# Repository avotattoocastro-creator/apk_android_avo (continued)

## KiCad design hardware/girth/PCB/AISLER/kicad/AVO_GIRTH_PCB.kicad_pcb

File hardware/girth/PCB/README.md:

# AVO GIRTH · placa de la cincha · REV B (ESP32-C3)

Placa propia para la cápsula de la cincha (REV 5.8.1), montada por JLCPCB: **una sola PCB de 4 capas** del tamaño de la
bandeja, con **conector para la batería** (JST SH 1,0) y **pads para soldar la bobina Qi** y el reed.

**Por qué REV B:** JLCPCB no tiene el ESP32-C6-MINI-1U-N4 de la REV A (0 uds. el 2026-10-29). La REV B usa el
**ESP32-C3-MINI-1U-N4** (C2911374, 1191 uds.), cambia el BNO085 (19,50 US$, 80 uds.) por **LSM6DS3TR-C + MMC5983MA**
y el relé biestable por un **enclavamiento con MOSFET**: mismas funciones, ~50 % menos de coste por placa
(`out_stock/COSTE.md`). La REV A queda congelada en `../PCB_REV_A_C6`.

**Estado:** diseño generado y comprobado en CI con KiCad 9 (`out/`). **NO VERIFICADO** en hardware: no se ha
fabricado ni medido ninguna placa.

## Qué lleva
| Bloque | Pieza | Notas |
|---|---|---|
| MCU | ESP32-C3-MINI-1U-N4 (U4) | antena externa por el conector de 3.ª generación del módulo (**W.FL / MHF III**, no U.FL). Alternativa: -H4 (C3013922, 105 °C, misma memoria) |
| IMU | LSM6DS3TR-C (U5) + MMC5983MA (U7) por **I²C** | 9 ejes brutos como pide el protocolo de la cincha; la huella de U5 admite el LSM6DSV16X |
| Qi | BQ51013B (U1), salida 5 V | bobina Ø25 a los pads L1/L2; condensadores de resonancia **a ajustar** (`DOCS/AJUSTE_QI.md`) |
| Carga | BQ24072 (U2) con camino de potencia | 270 mA de carga (0,54 C), entrada limitada a 462 mA (< 494 mA del Qi), NTC en placa (RT2) |
| USB-C | J1 + ESD (U6) | programación y consola; entra en el BQ51013B por AD/AD-EN (Q1/Q2) y **también carga** |
| 3,3 V | RT9080-33 (U3) | 600 mA, 2 µA de consumo propio |
| Batería | J2 JST SH 1,0 (pin 1 = +) | el cable pasa por la ranura fresada junto al borde −X |
| Reed | pads SW1/SW2 (SW2 al + de la batería) | enciende por flanco y se lee en GPIO1 (Q16) |
| **Corte de batería** | **Q10 (PMOS) + Q11 (NMOS) + D10–D13 (BAV70)** | **≤ 2 µA apagada** fuera del soporte (máx. de hoja a 25 °C; ≈ 7–8 µA dentro); ver abajo |

## Corte de batería (enclavamiento con MOSFET)
- **Se enciende solo**, sin firmware: al **cerrarse** el reed (C40 da un impulso de ≈ 2,5 s, con la corriente por el
  reed limitada a 19 mA y rearmado en ~2–3 s tras abrirse) o con 5 V de la base Qi o del USB (D10, mientras estén).
- **El firmware lo mantiene** con PWR_HOLD (GPIO5) = 1, que pone lo primero al arrancar. Si el ESP32 se reinicia, C41
  sostiene el corte ~1,2 s.
- **Se apaga desde el ESP32**: PWR_HOLD = 0 → el corte se abre en ~2,7 s. Funciona también con el reed cerrado (el reed
  actúa por flanco), así que el **apagado remoto** sigue siendo posible en el soporte.
- **Nunca queda bloqueado al cargar**: con 5 V presentes el corte está cerrado pase lo que pase en el firmware.
- **Batería agotada**: con la base puesta, el diodo interno de Q10 deja precargar la celda y luego Q10 conduce.
- Cálculos en `DOCS/ANALISIS_ELECTRICO.md` §3 (red del reed revisada tras una revisión independiente). Respecto al relé de la REV A: no necesita rebaje en la tapa ni
  condensadores de 220 µF, no tiene polaridad que adivinar (R40/R41 desaparecen) y no lleva imán junto a la IMU.

## Pines del ESP32-C3 (firmware V0.3.0: `firmware/girth/V0_3_0_C3`)
| GPIO | Función | Nota |
|---|---|---|
| 0 | IMU_INT (INT1 del LSM6) | despierta |
| 1 | REED (LOW = cápsula en el soporte) | despierta |
| 2 | I²C SCL | strapping: 1 al arrancar gracias al pull-up de 4,7 k |
| 3 | BAT_ADC (ADC1_CH3) | divisor 1 MΩ / 1 MΩ → V_bat / 2 |
| 4 | CHG_PG (LOW = hay 5 V) | despierta |
| 5 | PWR_HOLD | 1 = mantener la alimentación |
| 6 | I²C SDA | |
| 7 | CHG_STAT (LOW = cargando) | |
| 8 | LED rojo (activo bajo) | strapping: 1 al arrancar |
| 9 | BOOT (pad TP2) | strapping; 5 s pulsado = olvidar la espalda |
| 10 | QI_CHG (LOW = el Qi entrega potencia) | |
| 18 / 19 | USB D− / D+ | USB-Serial-JTAG |
| 20 / 21 | RXD0 / TXD0 (pads TP5 / TP4) | UART0 de la ROM: registro y recuperación |

**Reglas para el firmware:** PWR_HOLD = 1 lo primero; fuera del soporte 3 s sin carga → apagar; batería < 3,30 V →
apagar; en la base Qi fuera del soporte → sueño profundo. Detalle en `firmware/girth/V0_3_0_C3/DIFERENCIAS_C6_C3.md`.

## Programación y recuperación
Por el USB-C interno (USB-Serial-JTAG) con esptool o Arduino: `AVO_GIRTH_V0_3_0_C3_COMPLETO.bin` en 0x0. Si el
firmware no arranca: mantener BOOT (TP2) a masa al encender para entrar en modo descarga, o usar el UART0 (TP4/TP5).
**AVO Update todavía solo instala en el ESP32-C6**: hay que adaptarlo (id de chip 5 y vigilantes del C3) antes de
usarlo con esta placa.

## Consumo estimado
- **Apagada** (fuera del soporte): ≤ 2 µA (fugas de Q10 y de Q11 por R40, máx. de hoja a 25 °C; más con calor) + autodescarga de la celda. **Dentro del soporte** (reed
  cerrado): ≈ 7–8 µA por R45 y R49/R50 (simulado en la auditoría REV B, `AUDITORIA_REV_B/spice`).
- **Funcionando**: *corregido en la auditoría REV B* — con el firmware V0.3.0 (radio sin ahorro, `WIFI_PS_NONE`)
  ≈ 94 mA → **≈ 5 h** con 500 mAh (4 h con la celda envejecida); con ahorro de radio ≈ 45 mA → ≈ 10 h. Cálculo en
  `AUDITORIA_REV_B/autonomia/` (sin medir). La cifra anterior (25–45 mA, 11–20 h) no contaba el receptor encendido.
- **En la base Qi**: sueño profundo, lo alimenta la base.

## Cambios mecánicos que pide la placa (siguiente revisión del CAD de la cápsula)
1. **Cuna de la batería +0,6 mm** (apoyo de la placa a z 7,75): hueco bajo la placa para las patas del blindaje del
   USB-C. El techo sigue en z 13,2: quedan 4,1 mm sobre la placa (lo más alto es el USB-C, 3,3 mm).
2. **Labio de la tapa** apoyado sobre la placa, 0,6 mm más alto.
3. **Cable de la batería** por la ranura de la placa en (−29; 4,6). Hilos de la bobina a L1/L2 en X −28,6 e hilos
   del reed a SW1/SW2 en Y −17,8.
4. **Antena FPC** pegada al techo de la tapa sobre la banda sin cobre (X −3,3…25,5; Y 12,6 al borde).
5. **Postes de la tapa**: rehacerlos para que apoyen en zonas libres de la placa.
6. La bandeja impresa desaparece: la placa es la bandeja.
7. Ya **no** hace falta el rebaje de 1,3 mm de la REV A (no hay relé).

## Fabricación (JLCPCB)
- 4 capas, **1,0 mm**, ENIG, vías 0,3/0,5 mm, pista/separación mínimas 0,15 mm. Capas: F.Cu señal · In1.Cu plano
  GND · In2.Cu señal + relleno +3V3 · B.Cu señal + relleno GND.
- Ficheros, solo si la puerta del CI pasa, en `out/C3/`: `AVO_GIRTH_PCB_C3_GERBER_JLCPCB.zip`, `_BOM_JLCPCB.csv`,
  `_CPL_JLCPCB.csv`, `_STEP.step`, `_DRC.txt`, `_ERC.txt`, `_FIRMWARE.zip`, `_REPORTE.md`, fuentes de KiCad y
  `SHA256SUMS.txt`. Si falla, solo hay `out/AVO_GIRTH_PCB_C3_DIAGNOSTICO_REPORTE.md` y el job termina en rojo.
- Existencias, precios y tipo (Basic/Extended) consultados en el CI: `out_stock/stock_jlc.json` (con fecha);
  coste comparado con la REV A: `out_stock/COSTE.md`. **Volver a comprobar las existencias el día del pedido.**
- **Revisar el giro de cada pieza en la vista previa de JLCPCB** antes de pagar (sobre todo U1, U2, U4, U5, U7, U6,
  Q1–Q3, Q10, Q11, D10, D11, J1, J2, D1): el CPL sale de KiCad sin correcciones de giro.
- Piezas sin montar (DNP): C5.

## Medidas y comprobaciones pendientes
1. Inductancia de la bobina y ajuste de C1–C5 (`DOCS/AJUSTE_QI.md`).
2. Polaridad del cable de la batería contra J2 (pin 1 = +).
3. Corte de batería: tiempo de encendido con el reed, tiempo que sostiene un reinicio, tiempo de apagado y
   consumo apagado (≤ 2 µA esperado fuera del soporte, ≈ 7–8 µA con el reed cerrado).
4. Primer encendido con fuente limitada a 100 mA; medir 3,3 V, consumo dormido y carga por USB y por Qi.
5. IMU: direcciones I²C (`DIAG`), signos de los ejes y calibración del magnetómetro dentro de la cápsula.

## Fuentes del diseño
`fuente/avo_girth_pcb.py` (piezas, redes, colocación) → `fuente/build.py` (placa de colocación) +
`fuente/write_sch.py` (esquema, reglas, lista de piezas). Ruteado: Freerouting 1.9.0 en el CI sobre
`kicad/AVO_GIRTH_PCB_colocacion.kicad_pcb` y reparación de lo que deja sin unir con `fuente/repair.py`
(→ `kicad/AVO_GIRTH_PCB_ruteado.kicad_pcb`, que el CI usa tal cual si existe). El CI
(`.github/workflows/build-girth-pcb.yml`) rellena las zonas con KiCad 9, pasa DRC con paridad de esquema y ERC,
aplica la puerta bloqueante (`fuente/gate.py`) y solo entonces exporta los ficheros de fabricación.

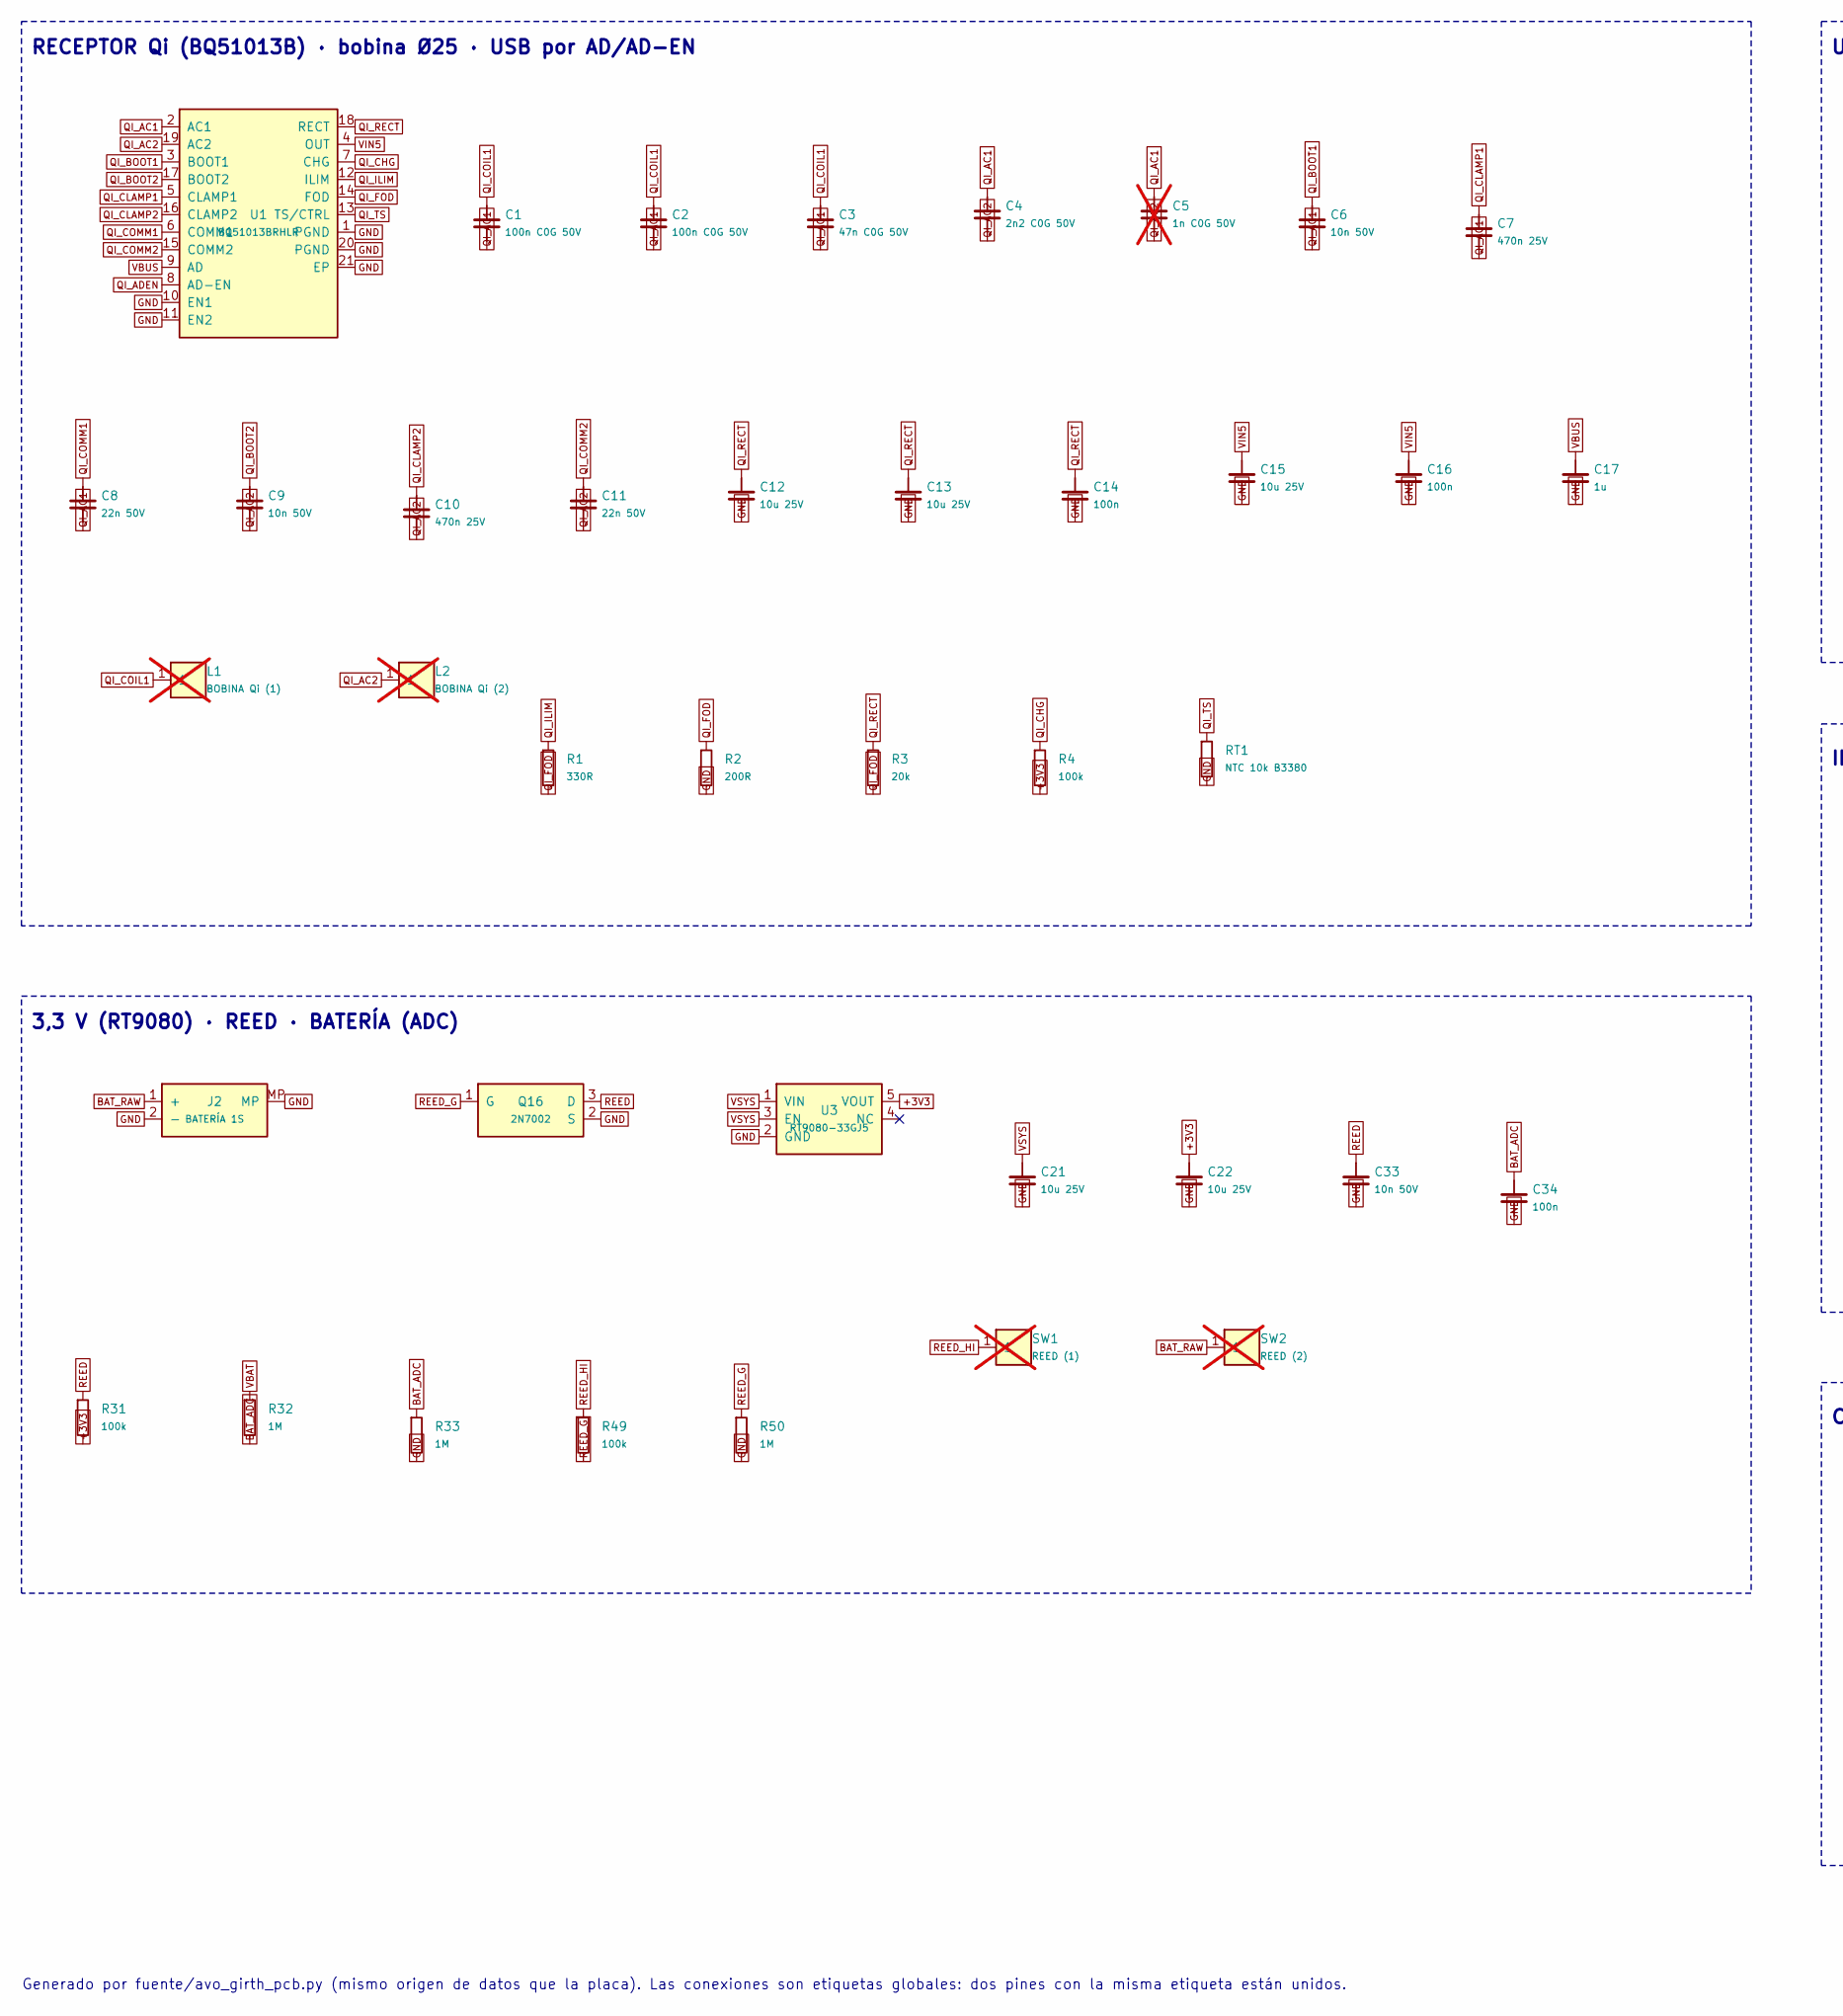
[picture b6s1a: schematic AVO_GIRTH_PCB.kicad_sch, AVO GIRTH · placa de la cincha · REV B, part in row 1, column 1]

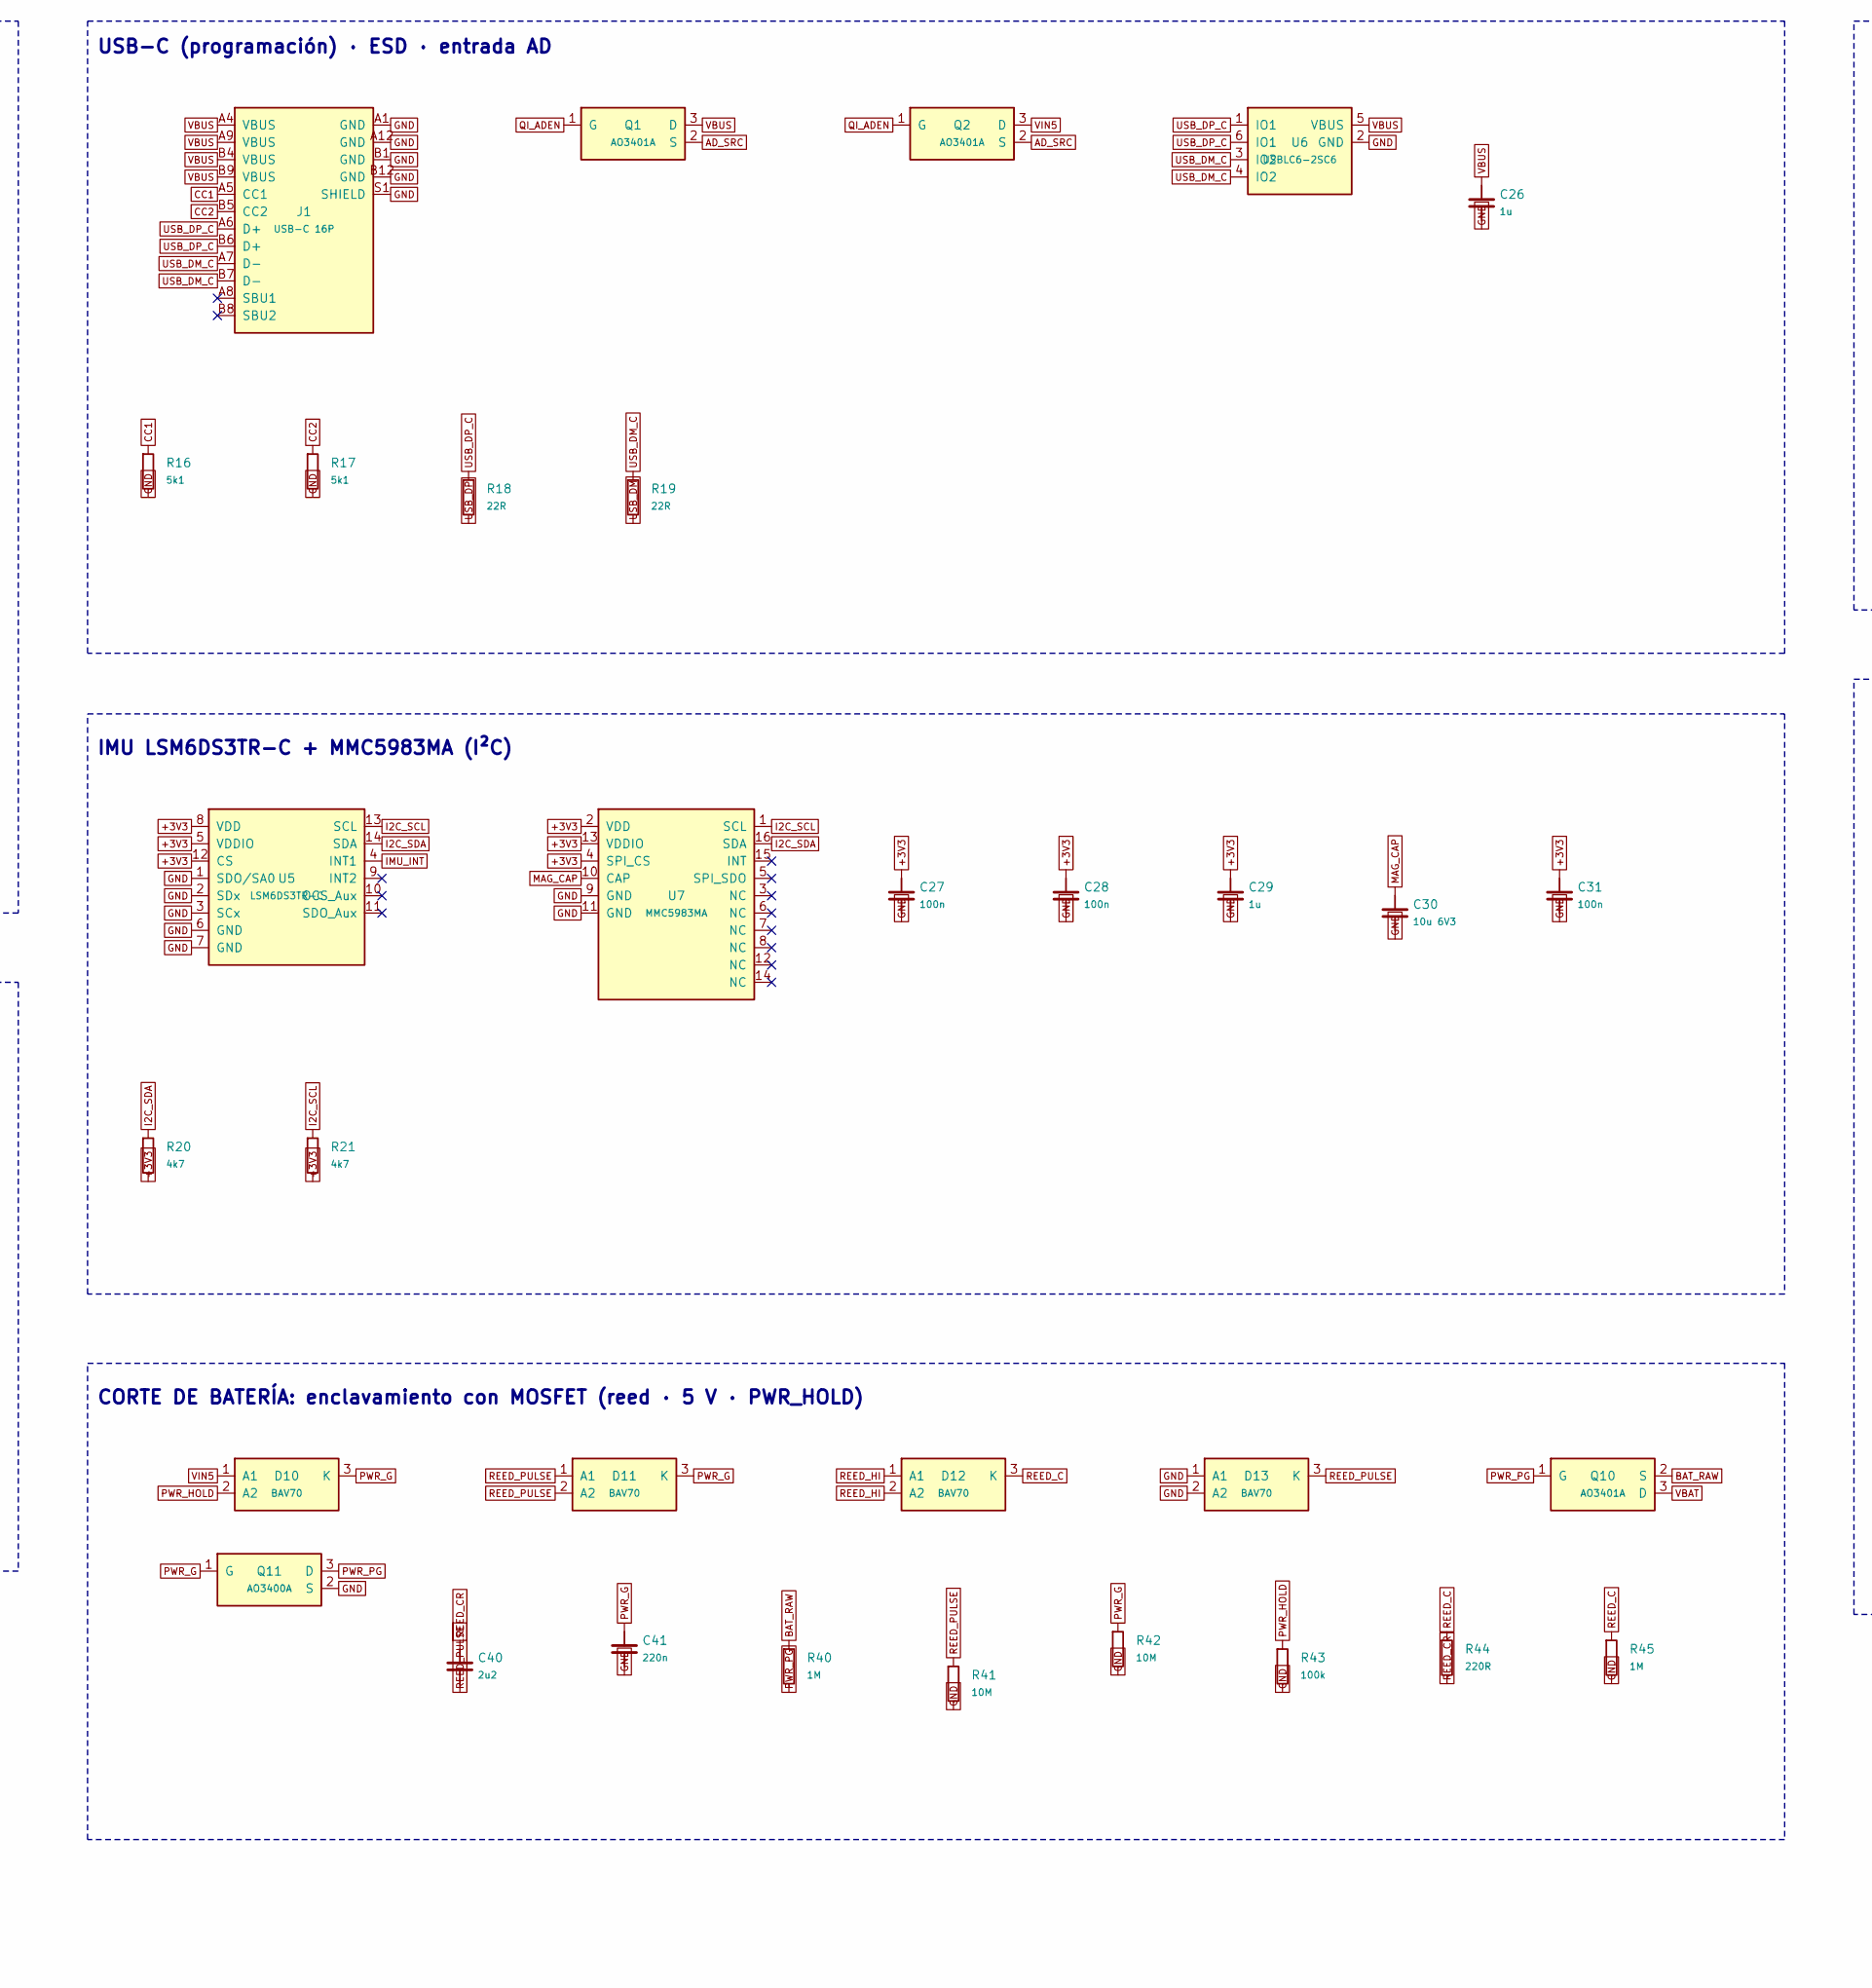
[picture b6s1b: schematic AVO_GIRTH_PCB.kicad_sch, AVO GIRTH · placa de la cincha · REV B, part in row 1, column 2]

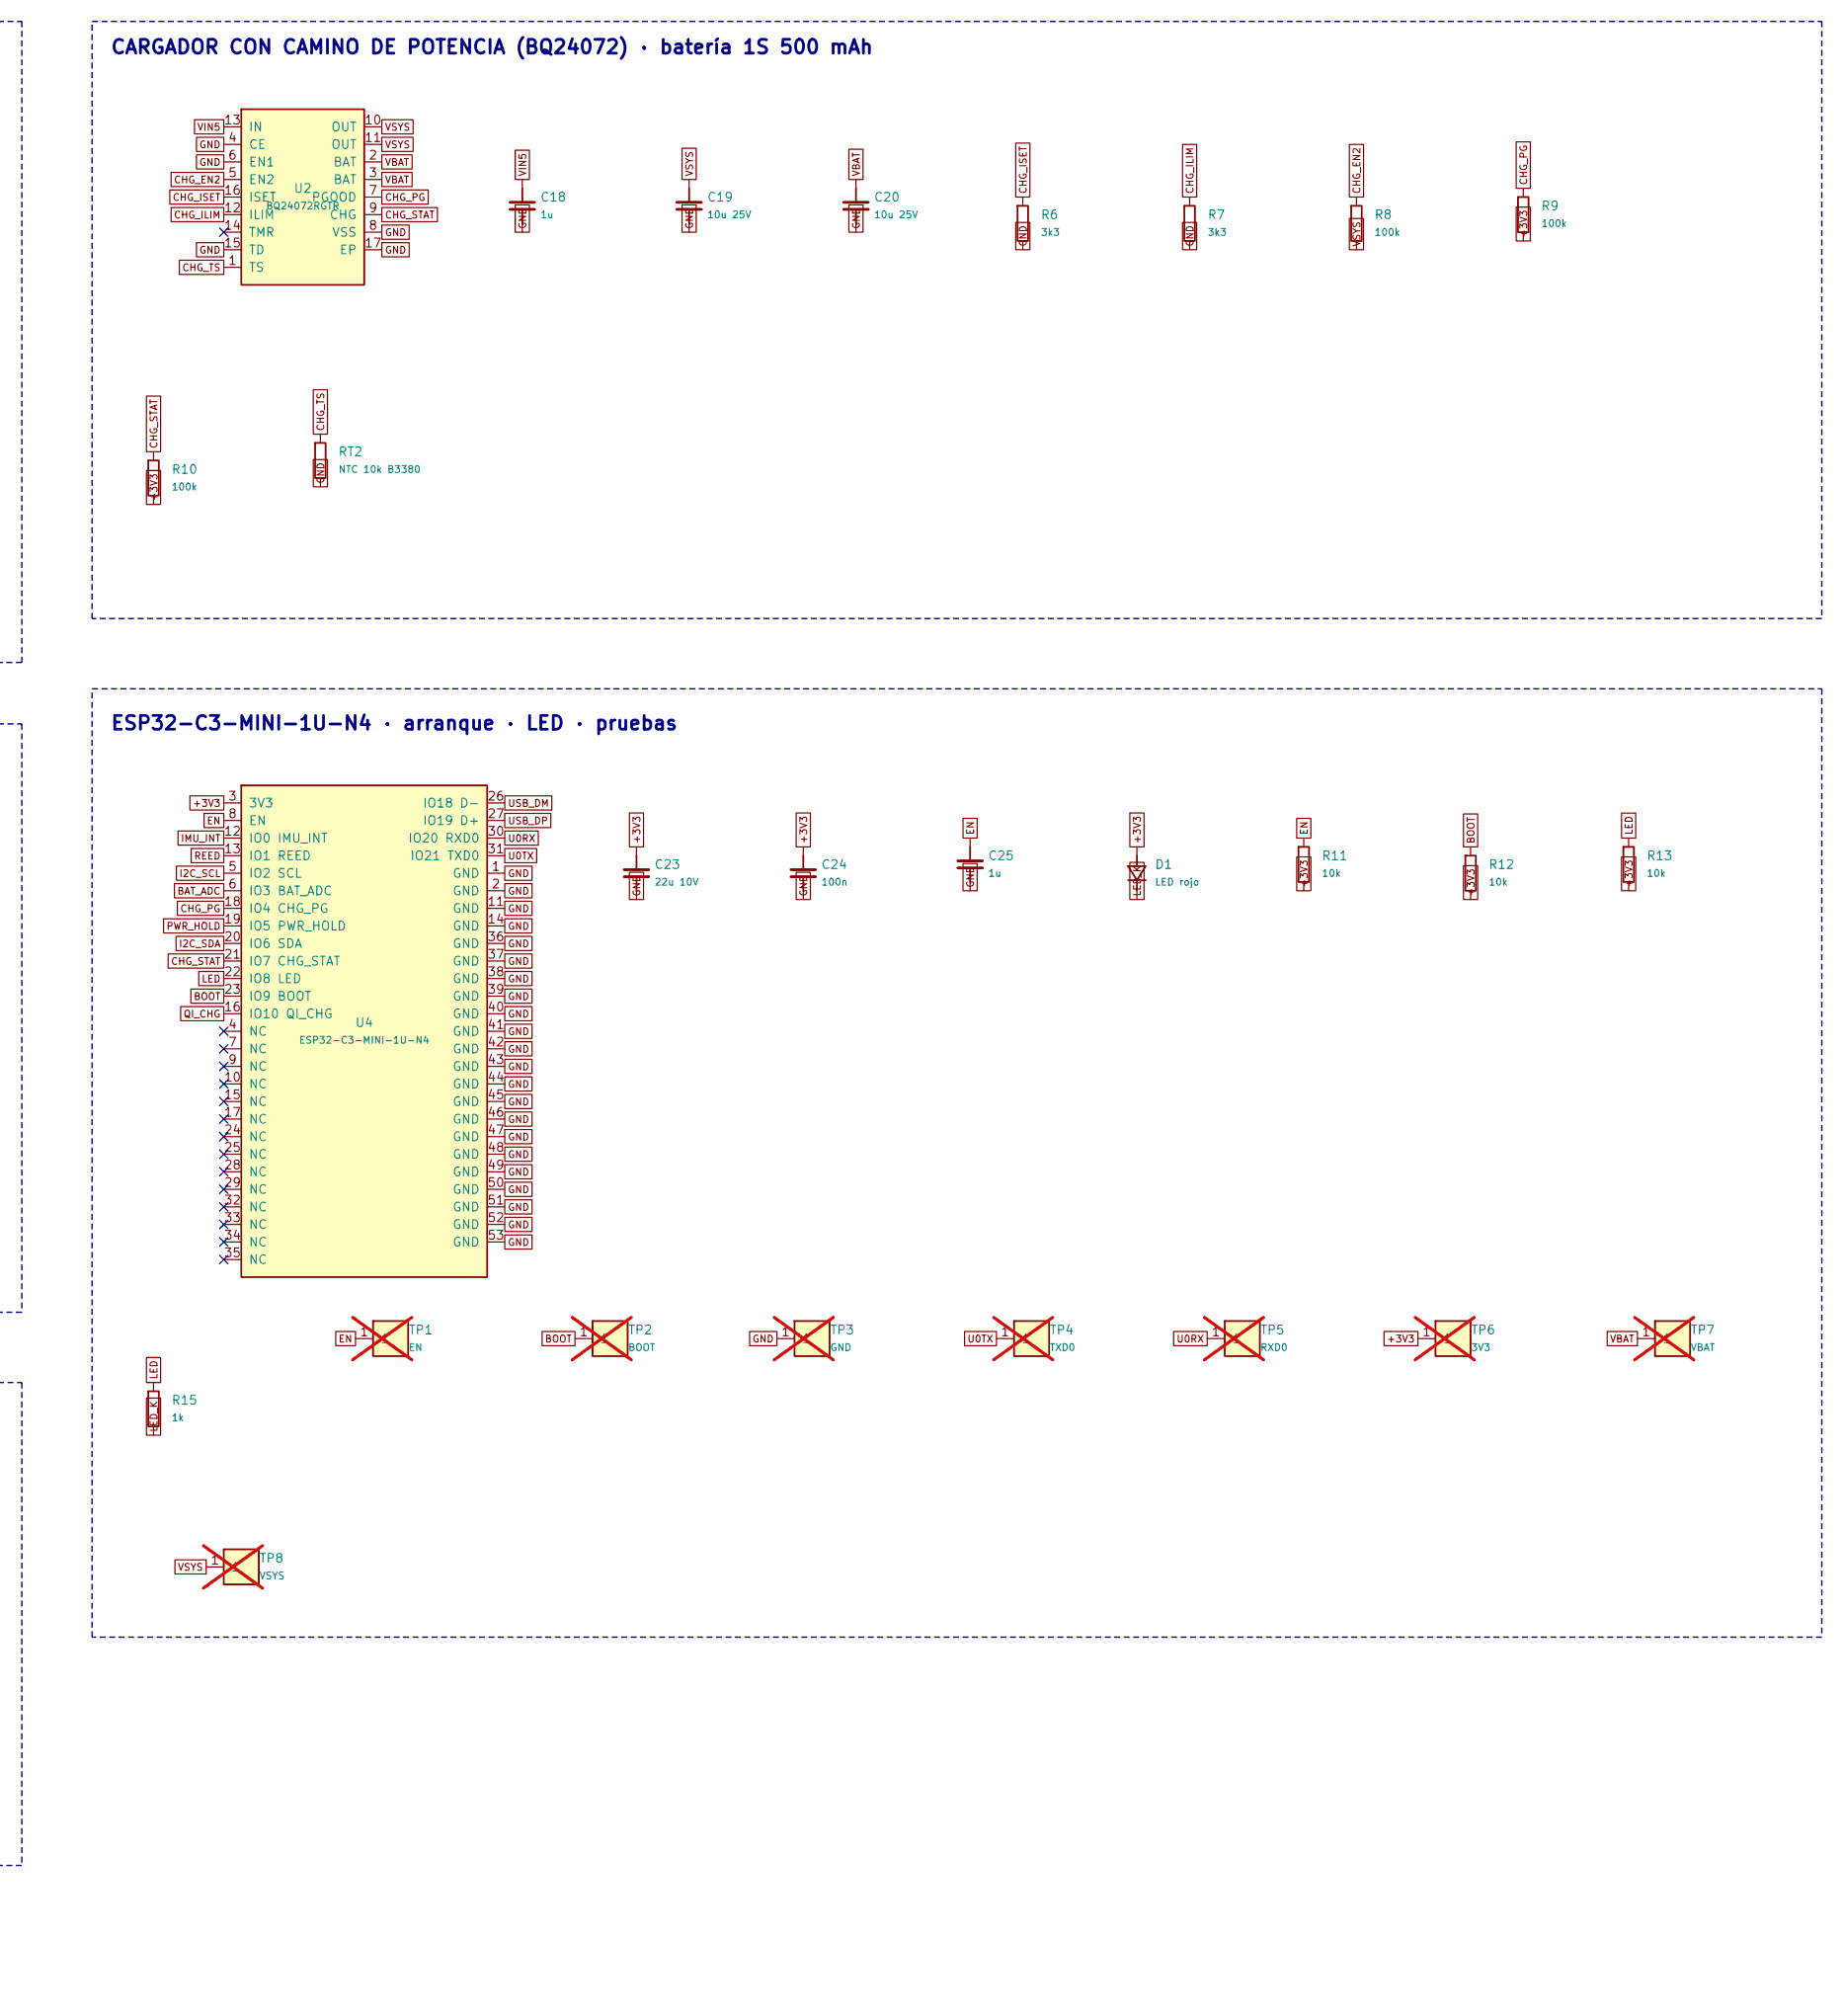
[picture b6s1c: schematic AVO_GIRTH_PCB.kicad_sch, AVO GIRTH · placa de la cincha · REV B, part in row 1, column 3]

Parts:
C1, C2: 100n C0G 50V; C_1206_3216Metric; LCSC C97946
C3: 47n C0G 50V; C_1206_3216Metric; LCSC C21812
C4: 2n2 C0G 50V; C_0805_2012Metric; LCSC C51795
C5: 1n C0G 50V; C_0603_1608Metric; LCSC C1636; not fitted
C6, C9, C33: 10n 50V; C_0402_1005Metric; LCSC C15195
C7, C10: 470n 25V; C_0603_1608Metric; LCSC C1623
C8, C11: 22n 50V; C_0402_1005Metric; LCSC C1532
C12, C13, C15, C19, C20, C21, C22: 10u 25V; C_0603_1608Metric; LCSC C96446
C14, C16, C24, C27, C28, C31, C34: 100n; C_0402_1005Metric; LCSC C1525
C17, C18, C25, C26, C29: 1u; C_0402_1005Metric; LCSC C52923
C23: 22u 10V; C_0805_2012Metric; LCSC C45783
C30: 10u 6V3; C_0603_1608Metric; LCSC C19702
C40: 2u2; C_0603_1608Metric; LCSC C23630
C41: 220n; C_0402_1005Metric; LCSC C16772
D1: LED rojo; LED_0603_1608Metric; MPN KT-0603R; LCSC C2286
D10, D11, D12, D13: BAV70; SOT-23; LCSC C68978
J1: USB-C 16P; USB_C_Receptacle_HRO_TYPE-C-31-M-12; MPN TYPE-C-31-M-12; LCSC C165948
J2: BATERÍA 1S; JST_SH_SM02B-SRSS-TB_1x02-1MP_P1.00mm_Horizontal; MPN SM02B-SRSS-TB (JST SH 1,0); LCSC C160402
L1: BOBINA Qi (1); WirePad_D1.5_Drill0.8; not fitted
L2: BOBINA Qi (2); WirePad_D1.5_Drill0.8; not fitted
Q1, Q2, Q10: AO3401A; SOT-23; LCSC C15127
Q11: AO3400A; SOT-23; LCSC C20917
Q16: 2N7002; SOT-23; LCSC C8545
R1: 330R; R_0402_1005Metric; LCSC C25104
R2: 200R; R_0402_1005Metric; LCSC C25087
R3: 20k; R_0402_1005Metric; LCSC C25765
R4, R8, R9, R10, R31, R43, R49: 100k; R_0402_1005Metric; LCSC C25741
R6, R7: 3k3; R_0402_1005Metric; LCSC C25890
R11, R12, R13: 10k; R_0402_1005Metric; LCSC C25744
R15: 1k; R_0402_1005Metric; LCSC C11702
R16, R17: 5k1; R_0402_1005Metric; LCSC C25905
R18, R19: 22R; R_0402_1005Metric; LCSC C25092
R20, R21: 4k7; R_0402_1005Metric; LCSC C25900
R32, R33, R40, R45, R50: 1M; R_0402_1005Metric; LCSC C26083
R41, R42: 10M; R_0402_1005Metric; LCSC C26082
R44: 220R; R_0402_1005Metric; LCSC C25091
RT1, RT2: NTC 10k B3380; R_0402_1005Metric; MPN NCP15XH103F03RC; LCSC C77131
SW1: REED (1); WirePad_D1.5_Drill0.8; not fitted
SW2: REED (2); WirePad_D1.5_Drill0.8; not fitted
TP1: EN; TestPoint_Pad_D1.0mm; not fitted
TP2: BOOT; TestPoint_Pad_D1.0mm; not fitted
TP3: GND; TestPoint_Pad_D1.0mm; not fitted
TP4: TXD0; TestPoint_Pad_D1.0mm; not fitted
TP5: RXD0; TestPoint_Pad_D1.0mm; not fitted
TP6: 3V3; TestPoint_Pad_D1.0mm; not fitted
TP7: VBAT; TestPoint_Pad_D1.0mm; not fitted
TP8: VSYS; TestPoint_Pad_D1.0mm; not fitted
U1: BQ51013BRHLR; Texas_VQFN-RHL-20_ThermalVias; MPN BQ51013BRHLR (alt. BQ51013CRHLR C430435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; LCSC C55663
U2: BQ24072RGTR; VQFN-16-1EP_3x3mm_P0.5mm_EP1.68x1.68mm_ThermalVias; MPN BQ24072RGTR; LCSC C140288
U3: RT9080-33GJ5; SOT-23-5; MPN RT9080-33GJ5; LCSC C841192
U4: ESP32-C3-MINI-1U-N4; ESP32-C3-MINI-1U; MPN ESP32-C3-MINI-1U-N4 (alt. ESP32-C3-MINI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; LCSC C2911374
U5: LSM6DS3TR-C; ST_LGA-14L_2.5x3mm_P0.5mm; MPN LSM6DS3TR-C (alt. LSM6DSV16XTR C5267406); LCSC C967633
U6: USBLC6-2SC6; SOT-23-6; LCSC C7519
U7: MMC5983MA; MEMSIC_MMC5983MA_LGA-16_3x3mm_P0.5mm; MPN MMC5983MA; LCSC C404329

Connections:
+3V3: C22.1, C23.1, C24.1, C27.1, C28.1, C29.1, C31.1, D1.2 (A), R4.2, R9.2, R10.2, R11.2, R12.2, R13.2, R20.2, R21.2, R31.2, TP6.1, U3.5 (VOUT), U4.3 (3V3), U5.5 (VDDIO), U5.8 (VDD), U5.12 (CS), U7.2 (VDD), U7.4 (SPI_CS), U7.13 (VDDIO)
AD_SRC: Q1.2 (S), Q2.2 (S)
BAT_ADC: C34.1, R32.2, R33.1, U4.6 (IO3 BAT_ADC)
BAT_RAW: J2.1 (+), Q10.2 (S), R40.1, SW2.1
BOOT: R12.1, TP2.1, U4.23 (IO9 BOOT)
CC1: J1.A5 (CC1), R16.1
CC2: J1.B5 (CC2), R17.1
CHG_EN2: R8.1, U2.5 (EN2)
CHG_ILIM: R7.1, U2.12 (ILIM)
CHG_ISET: R6.1, U2.16 (ISET)
CHG_PG: R9.1, U2.7 (PGOOD), U4.18 (IO4 CHG_PG)
CHG_STAT: R10.1, U2.9 (CHG), U4.21 (IO7 CHG_STAT)
CHG_TS: RT2.1, U2.1 (TS)
EN: C25.1, R11.1, TP1.1, U4.8 (EN)
GND: C12.2, C13.2, C14.2, C15.2, C16.2, C17.2, C18.2, C19.2, C20.2, C21.2, C22.2, C23.2, C24.2, C25.2, C26.2, C27.2, C28.2, C29.2, C30.2, C31.2, C33.2, C34.2, C41.2, D13.1 (A1), D13.2 (A2), J1.A1 (GND), J1.A12 (GND), J1.B1 (GND), J1.B12 (GND), J1.S1 (SHIELD), J2.2 (−), J2.MP, Q11.2 (S), Q16.2 (S), R2.2, R6.2, R7.2, R16.2, R17.2, R33.2, R41.2, R42.2, R43.2, R45.2, R50.2, RT1.2, RT2.2, TP3.1, U1.1 (PGND), U1.10 (EN1), U1.11 (EN2), U1.20 (PGND), U1.21 (EP), U2.4 (CE), U2.6 (EN1), U2.8 (VSS), U2.15 (TD), U2.17 (EP), U3.2 (GND), U4.1 (GND), U4.2 (GND), U4.11 (GND), U4.14 (GND), U4.36 (GND), U4.37 (GND), U4.38 (GND), U4.39 (GND), U4.40 (GND), U4.41 (GND), U4.42 (GND), U4.43 (GND), U4.44 (GND), U4.45 (GND), U4.46 (GND), U4.47 (GND), U4.48 (GND), U4.49 (GND), U4.50 (GND), U4.51 (GND), U4.52 (GND), U4.53 (GND), U5.1 (SDO/SA0), U5.2 (SDx), U5.3 (SCx), U5.6 (GND), U5.7 (GND), U6.2 (GND), U7.9 (GND), U7.11 (GND)
I2C_SCL: R21.1, U4.5 (IO2 SCL), U5.13 (SCL), U7.1 (SCL)
I2C_SDA: R20.1, U4.20 (IO6 SDA), U5.14 (SDA), U7.16 (SDA)
IMU_INT: U4.12 (IO0 IMU_INT), U5.4 (INT1)
LED: R13.1, R15.1, U4.22 (IO8 LED)
LED_K: D1.1 (K), R15.2
MAG_CAP: C30.1, U7.10 (CAP)
PWR_G: C41.1, D10.3 (K), D11.3 (K), Q11.1 (G), R42.1
PWR_HOLD: D10.2 (A2), R43.1, U4.19 (IO5 PWR_HOLD)
PWR_PG: Q10.1 (G), Q11.3 (D), R40.2
QI_AC1: C1.2, C2.2, C3.2, C4.1, C5.1, C6.2, C7.2, C8.2, U1.2 (AC1)
QI_AC2: C4.2, C5.2, C9.2, C10.2, C11.2, L2.1, U1.19 (AC2)
QI_ADEN: Q1.1 (G), Q2.1 (G), U1.8 (AD-EN)
QI_BOOT1: C6.1, U1.3 (BOOT1)
QI_BOOT2: C9.1, U1.17 (BOOT2)
QI_CHG: R4.1, U1.7 (CHG), U4.16 (IO10 QI_CHG)
QI_CLAMP1: C7.1, U1.5 (CLAMP1)
QI_CLAMP2: C10.1, U1.16 (CLAMP2)
QI_COIL1: C1.1, C2.1, C3.1, L1.1
QI_COMM1: C8.1, U1.6 (COMM1)
QI_COMM2: C11.1, U1.15 (COMM2)
QI_FOD: R1.2, R2.1, R3.2, U1.14 (FOD)
QI_ILIM: R1.1, U1.12 (ILIM)
QI_RECT: C12.1, C13.1, C14.1, R3.1, U1.18 (RECT)
QI_TS: RT1.1, U1.13 (TS/CTRL)
REED: C33.1, Q16.3 (D), R31.1, U4.13 (IO1 REED)
REED_C: D12.3 (K), R44.1, R45.1
REED_CR: C40.1, R44.2
REED_G: Q16.1 (G), R49.2, R50.1
REED_HI: D12.1 (A1), D12.2 (A2), R49.1, SW1.1
REED_PULSE: C40.2, D11.1 (A1), D11.2 (A2), D13.3 (K), R41.1
U0RX: TP5.1, U4.30 (IO20 RXD0)
U0TX: TP4.1, U4.31 (IO21 TXD0)
USB_DM: R19.2, U4.26 (IO18 D-)
USB_DM_C: J1.A7 (D−), J1.B7 (D−), R19.1, U6.3 (IO2), U6.4 (IO2)
USB_DP: R18.2, U4.27 (IO19 D+)
USB_DP_C: J1.A6 (D+), J1.B6 (D+), R18.1, U6.1 (IO1), U6.6 (IO1)
VBAT: C20.1, Q10.3 (D), R32.1, TP7.1, U2.2 (BAT), U2.3 (BAT)
VBUS: C17.1, C26.1, J1.A4 (VBUS), J1.A9 (VBUS), J1.B4 (VBUS), J1.B9 (VBUS), Q1.3 (D), U1.9 (AD), U6.5 (VBUS)
VIN5: C15.1, C16.1, C18.1, D10.1 (A1), Q2.3 (D), U1.4 (OUT), U2.13 (IN)
VSYS: C19.1, C21.1, R8.2, TP8.1, U2.10 (OUT), U2.11 (OUT), U3.1 (VIN), U3.3 (EN)

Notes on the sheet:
CORTE DE BATERÍA: enclavamiento con MOSFET (reed · 5 V · PWR_HOLD)
USB-C (programación) · ESD · entrada AD
3,3 V (RT9080) · REED · BATERÍA (ADC)
RECEPTOR Qi (BQ51013B) · bobina Ø25 · USB por AD/AD-EN
CARGADOR CON CAMINO DE POTENCIA (BQ24072) · batería 1S 500 mAh
ESP32-C3-MINI-1U-N4 · arranque · LED · pruebas
IMU LSM6DS3TR-C + MMC5983MA (I²C)
Generado por fuente/avo_girth_pcb.py (mismo origen de datos que la placa). Las conexiones son etiquetas globales: dos pines con la misma etiqueta están unidos.
